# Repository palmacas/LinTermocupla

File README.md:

# LinTermocupla

The board reads the voltaje from a thermocouple (type J or K) and linearizes the temperature. The circuit is based on a PIC16F877a and includes a resistor-based digital-to-analog converter, so the linearized temperature value can be read by a PLC.

---
More information:  
[Linealizar una Termocupla [Spanish]](https://palmacas.com/linealizar-una-termocupla/)

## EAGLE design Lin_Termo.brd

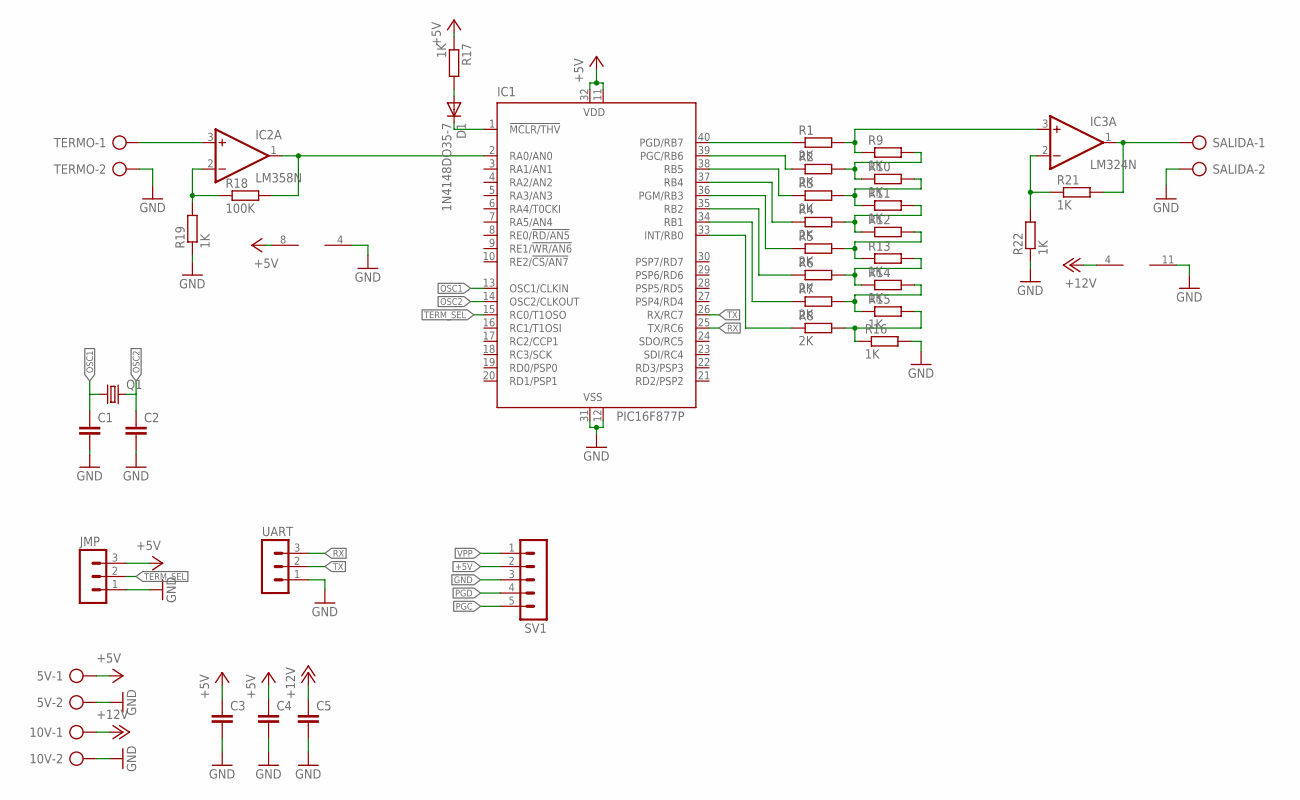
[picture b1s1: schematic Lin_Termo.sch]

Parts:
5V, 10V: AK500/2
C1, C2, C3, C4, C5: C-EU025-025X050; C025-025X050
D1: 1N4148DO35-7; DO35-7
IC1: PIC16F877P; DIL40
IC2: LM358N; DIL08
IC3: LM324N; DIL14
JMP: MA03-1
Q1: CRYSTALHC49S; HC49/S
R1, R2, R3, R4, R5, R6, R7, R8: 2K; 0207/2V
R9, R10, R11, R13, R14, R15, R16: 1K; 0207/2V
R12: R-EU_0207/2V; 0207/2V
R17, R19, R21, R22: 1K; 0207/7
R18: 100K; 0207/7
SALIDA: AK500/2
SV1: MA05-1
TERMO: AK500/2
UART: MA03-1

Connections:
+5V: 5V.1, C3.1, C4.1, IC1.11 (VDD), IC1.32 (VDD), IC2.8 (V+), JMP.3, R17.1, SV1.2
+12V: 10V.1, C5.1, IC3.4 (V+)
GND: 5V.2, 10V.2, C1.2, C2.2, C3.2, C4.2, C5.2, IC1.12 (VSS), IC1.31 (VSS), IC2.4 (V-), IC3.11 (V-), JMP.1, R16.2, R19.1, R22.1, SALIDA.2, SV1.3, TERMO.2, UART.1
unnamed: IC3.3 (+IN), R1.2, R9.1
unnamed: R2.2, R9.2, R10.1
unnamed: R3.2, R10.2, R11.1
unnamed: R4.2, R11.2, R12.1
unnamed: R5.2, R12.2, R13.1
unnamed: R6.2, R13.2, R14.1
unnamed: R7.2, R14.2, R15.1
unnamed: D1.A, R17.2
unnamed: IC1.38 (RB5), R3.1
unnamed: IC1.37 (RB4), R4.1
unnamed: IC1.36 (PGM/RB3), R5.1
unnamed: IC1.35 (RB2), R6.1
unnamed: IC1.34 (RB1), R7.1
unnamed: IC1.33 (INT/RB0), R8.1
unnamed: IC1.2 (RA0/AN0), IC2.1 (OUT), R18.2
unnamed: IC2.2 (-IN), R18.1, R19.2
unnamed: IC2.3 (+IN), TERMO.1
unnamed: R8.2, R15.2, R16.1
unnamed: IC3.2 (-IN), R21.1, R22.2
unnamed: IC3.1 (OUT), R21.2, SALIDA.1
OSC1: C1.1, IC1.13 (OSC1/CLKIN), Q1.1
OSC2: C2.1, IC1.14 (OSC2/CLKOUT), Q1.2
PGC: IC1.39 (PGC/RB6), R2.1, SV1.5
PGD: IC1.40 (PGD/RB7), R1.1, SV1.4
RX: IC1.25 (TX/RC6), UART.3
TERM_SEL: IC1.15 (RC0/T1OSO), JMP.2
TX: IC1.26 (RX/RC7), UART.2
VPP: D1.C, IC1.1 (!MCLR/THV), SV1.1

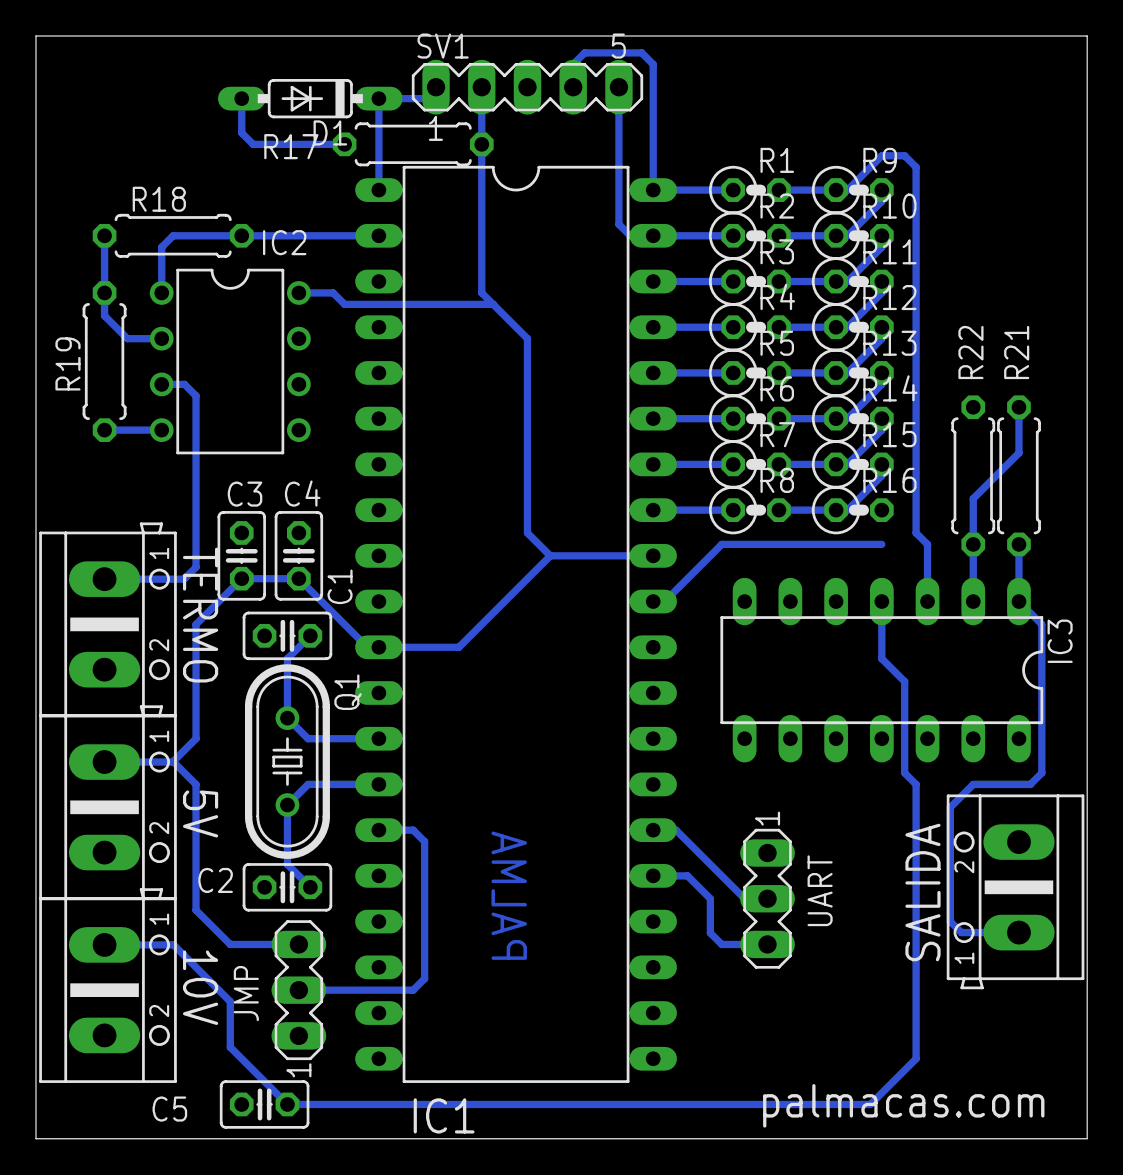
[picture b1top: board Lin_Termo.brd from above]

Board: 2 copper layers, 58.4 x 61.3 mm, 38 parts (0 on the bottom side), 31 nets.

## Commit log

2020-05-20 Create LICENSE
2020-05-20 Rename Lin_Termo.brd to board/Lin_Termo.brd
2020-05-20 Rename Lin_Termo.sch to board/Lin_Termo.sch
2020-05-21 Code update
2020-06-03 Update LICENSE
2022-08-21 Rename code/lin_termocupla.hex to Firmware/lin_termocupla.hex
2022-08-21 Rename code/lin_termocupla.c to Firmware/lin_termocupla.c
2022-08-21 Rename Firmware/lin_termocupla.hex to firmware/lin_termocupla.hex
2022-08-21 Rename Firmware/lin_termocupla.c to firmware/lin_termocupla.c
